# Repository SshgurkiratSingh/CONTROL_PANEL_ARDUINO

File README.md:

# Software-Defined Hardware Control Panel (SDH-CP)

An integrated, multi-interface hardware control platform that bridges physical inputs, microcontrollers, desktop GUIs, and web services. The project features an **Arduino-based firmware** with a rotary encoder and I2C OLED display, a **KiCad PCB design**, a **Python Tkinter Desktop GUI** featuring a background **Flask REST API**, and a **MATLAB dashboard**.

---

## Repository Structure

```directory
├── Software-Defined Hardware Control Panel/ # KiCad PCB & Schematic Design Files
│   ├── Software-Defined Hardware Control Panel.kicad_sch  # KiCad Schematic
│   ├── Software-Defined Hardware Control Panel.kicad_pcb  # KiCad PCB Layout
│   └── bom/
│       └── ibom.html                                       # Interactive Bill of Materials (iBOM)
├── src/                                     # Arduino C++ Firmware Source
│   ├── main.cpp                             # Main firmware loop and state machine
│   ├── helpers.cpp                          # RAM and hardware utility helpers
│   └── helpers.h                            # Circular Parameter Store class definitions
├── lib/                                     # Custom Hardware Libraries
│   └── ssd1306_128x64_i2c/                  # Optimized SSD1306 OLED display driver
├── include/                                 # PlatformIO headers directory
├── platformio.ini                           # PlatformIO Project Configuration
├── writeCommand.py                          # Python Tkinter GUI & Flask REST API Service
├── arduinoAMC.mlapp                         # MATLAB App Designer control panel/dashboard
├── package.json                             # Node.js dependencies (serialport tools)
└── README.md                                # Project Documentation (This file)
```

---

## Key Features

### Firmware (Arduino Uno + C++)
- **Dynamic Parameter Store**: Manages up to 5 runtime parameters (e.g., setpoints, configuration coefficients) with safety bounds (minimum and maximum).
- **Dual Display Modes**:
  - `MODE_FULL`: Shows the parameter name, current value, visual progress bar, and active connected software name.
  - `MODE_RAPID`: Switches to large-format value-only rendering during quick rotary encoder scrolls, reducing display redraw lag and maximizing responsiveness.
- **Hardware Integration**: Uses interrupt/tick-based rotary encoder tracking and switch inputs.
- **Real-Time Remote Control**: Provides a clean CSV-style serial communication protocol running at 9600 baud.

### Python GUI & REST API Daemon (writeCommand.py)
- **Desktop Console**: Multi-tab GUI for adding, reading, and updating parameters in real time. Contains a live serial traffic log and manual serial command terminal.
- **On-Demand Pin Reader**: Direct interface to read analog (A0-A5) and digital (D2-D13) pins on the fly.
- **REST API Backend**: Exposes a background Flask HTTP server on port `5000` to allow web apps or script automation to read and modify hardware states over simple network requests.

### Hardware Design (KiCad)
- Complete schematic and PCB design files for a dedicated control panel shield/device.
- **Interactive BOM (iBOM)** included (`ibom.html`) for easy assembly and soldering.

#### Hardware Gallery

| PCB 3D Render | PCB Routing |
| :---: | :---: |
|  |  |

| Schematic Diagram |
| :---: |
|  |

### MATLAB Integration (arduinoAMC.mlapp)
- Companion app for control, automation, and visualization of parameter values directly in MATLAB.

---

## Serial Communication Protocol

The Arduino firmware communicates with host computers via **9600 baud serial connection**. Messages use a command-response format:

### Host Commands (Commands sent to Arduino)

| Command Format | Description | Example |
| :--- | :--- | :--- |
| `add:param,<name>,<min>,<max>,<cur>` | Register/Overwrite a parameter in the store | `add:param,Gain,0,100,50` |
| `get:paramCurval,<name>` | Query the current value of a parameter | `get:paramCurval,Gain` |
| `update:paramsCurval,<name>,<val>` | Force-update a parameter value | `update:paramsCurval,Gain,65` |
| `get:AlladdedParams` | List all parameters in the store | `get:AlladdedParams` |
| `set:software,<name>` | Display active host software on the OLED | `set:software,MATLAB_App` |
| `read:digital,<pin>` | Set digital `<pin>` to input and read state | `read:digital,7` |
| `read:analog,<index>` | Read analog pin value (A0 + `<index>`) | `read:analog,0` |

### Arduino Responses & Broadcasts

| Response Prefix | Meaning | Format / Response Example |
| :--- | :--- | :--- |
| `A,<name>` | Parameter successfully added | `A,Gain` |
| `U,<name>,<val>` | Parameter updated (via encoder or serial command) | `U,Gain,65` |
| `S,<index>,<name>,<val>` | Active parameter selection cycled (via button press) | `S,0,Gain,65` |
| `G,<name>,<val>` | Parameter query result | `G,Gain,65` |
| `L,<idx>,<name>,<min>,<max>,<val>` | Parameter listing detail | `L,0,Gain,0,100,65` |
| `D,<pin>,<val>` | Digital pin read result | `D,7,1` |
| `A,<index>,<val>` | Analog pin read result | `A,0,512` |
| `ERR,<message>` | Command processing error | `ERR,Unknown command` |

---

## REST API Documentation

When running `writeCommand.py`, a Flask API server starts automatically at `http://localhost:5000`.

### Endpoints

#### 1. Get All Parameters
- **URL**: `/parameters`
- **Method**: `GET`
- **Response Example**:
  ```json
  {
    "Gain": {
      "index": "0",
      "min": "0",
      "max": "100",
      "current": 65
    }
  }
  ```

#### 2. Get Single Parameter
- **URL**: `/parameter/<name>`
- **Method**: `GET`
- **Response Example**:
  ```json
  {
    "Gain": {
      "index": "0",
      "min": "0",
      "max": "100",
      "current": 65
    }
  }
  ```

#### 3. Add Parameter
- **URL**: `/parameters`
- **Method**: `POST`
- **Headers**: `Content-Type: application/json`
- **Payload**:
  ```json
  {
    "name": "Frequency",
    "min": 10,
    "max": 1000,
    "current": 100
  }
  ```
- **Response**: `{"status": "Command sent", "command": "..."}`

#### 4. Update Parameter Value
- **URL**: `/parameter/<name>`
- **Method**: `PUT`
- **Headers**: `Content-Type: application/json`
- **Payload**:
  ```json
  {
    "new_value": 75
  }
  ```
- **Response**: `{"status": "Command sent", "command": "..."}`

#### 5. Send Raw Serial Command
- **URL**: `/command`
- **Method**: `POST`
- **Payload**: `{"command": "read:analog,0"}`
- **Response**: `{"status": "Command sent", "command": "..."}`

#### 6. Set Active Software Name
- **URL**: `/software`
- **Method**: `POST`
- **Payload**: `{"software_name": "API_Client"}`

#### 7. Retrieve Live GUI Console Log
- **URL**: `/log`
- **Method**: `GET`
- **Response**: `{"log": "..."}`

---

## Setup and Installation

### 1. Hardware Assembly
- Open the KiCad project files inside `Software-Defined Hardware Control Panel/` in KiCad.
- Reference the interactive BOM under `bom/ibom.html` for component lists and layout locations.
- Connect an I2C SSD1306 OLED screen to pins `SDA` (A4) and `SCL` (A5) of your Arduino.
- Connect a Rotary Encoder:
  - CLK to Pin 3 (Interrupt enabled)
  - DT to Pin 4
  - Push Button to Pin 2 (Interrupt/cycle pin)

### 2. Firmware Installation (VS Code + PlatformIO)
1. Open the project folder in VS Code with the **PlatformIO IDE** extension installed.
2. PlatformIO will fetch dependencies (`mathertel/RotaryEncoder`, `bblanchon/ArduinoJson`) automatically.
3. Build and upload:
   ```bash
   pio run --target upload
   ```

### 3. Desktop GUI & REST API Setup
Install python dependencies:
```bash
pip install pyserial flask
```
Identify your Arduino serial port (e.g. `/dev/ttyUSB0` on Linux or `COM3` on Windows). Update the default port at the bottom of `writeCommand.py` or launch the script:
```bash
python writeCommand.py
```

### 4. MATLAB Integration
- Launch MATLAB.
- Double-click and open `arduinoAMC.mlapp` in the App Designer to run the companion dashboard.

---

> [!NOTE]
> Ensure that no other program (such as VS Code Serial Monitor or MATLAB) is occupying the serial port when executing `writeCommand.py`, as only one application can hold the serial connection handle at a time.

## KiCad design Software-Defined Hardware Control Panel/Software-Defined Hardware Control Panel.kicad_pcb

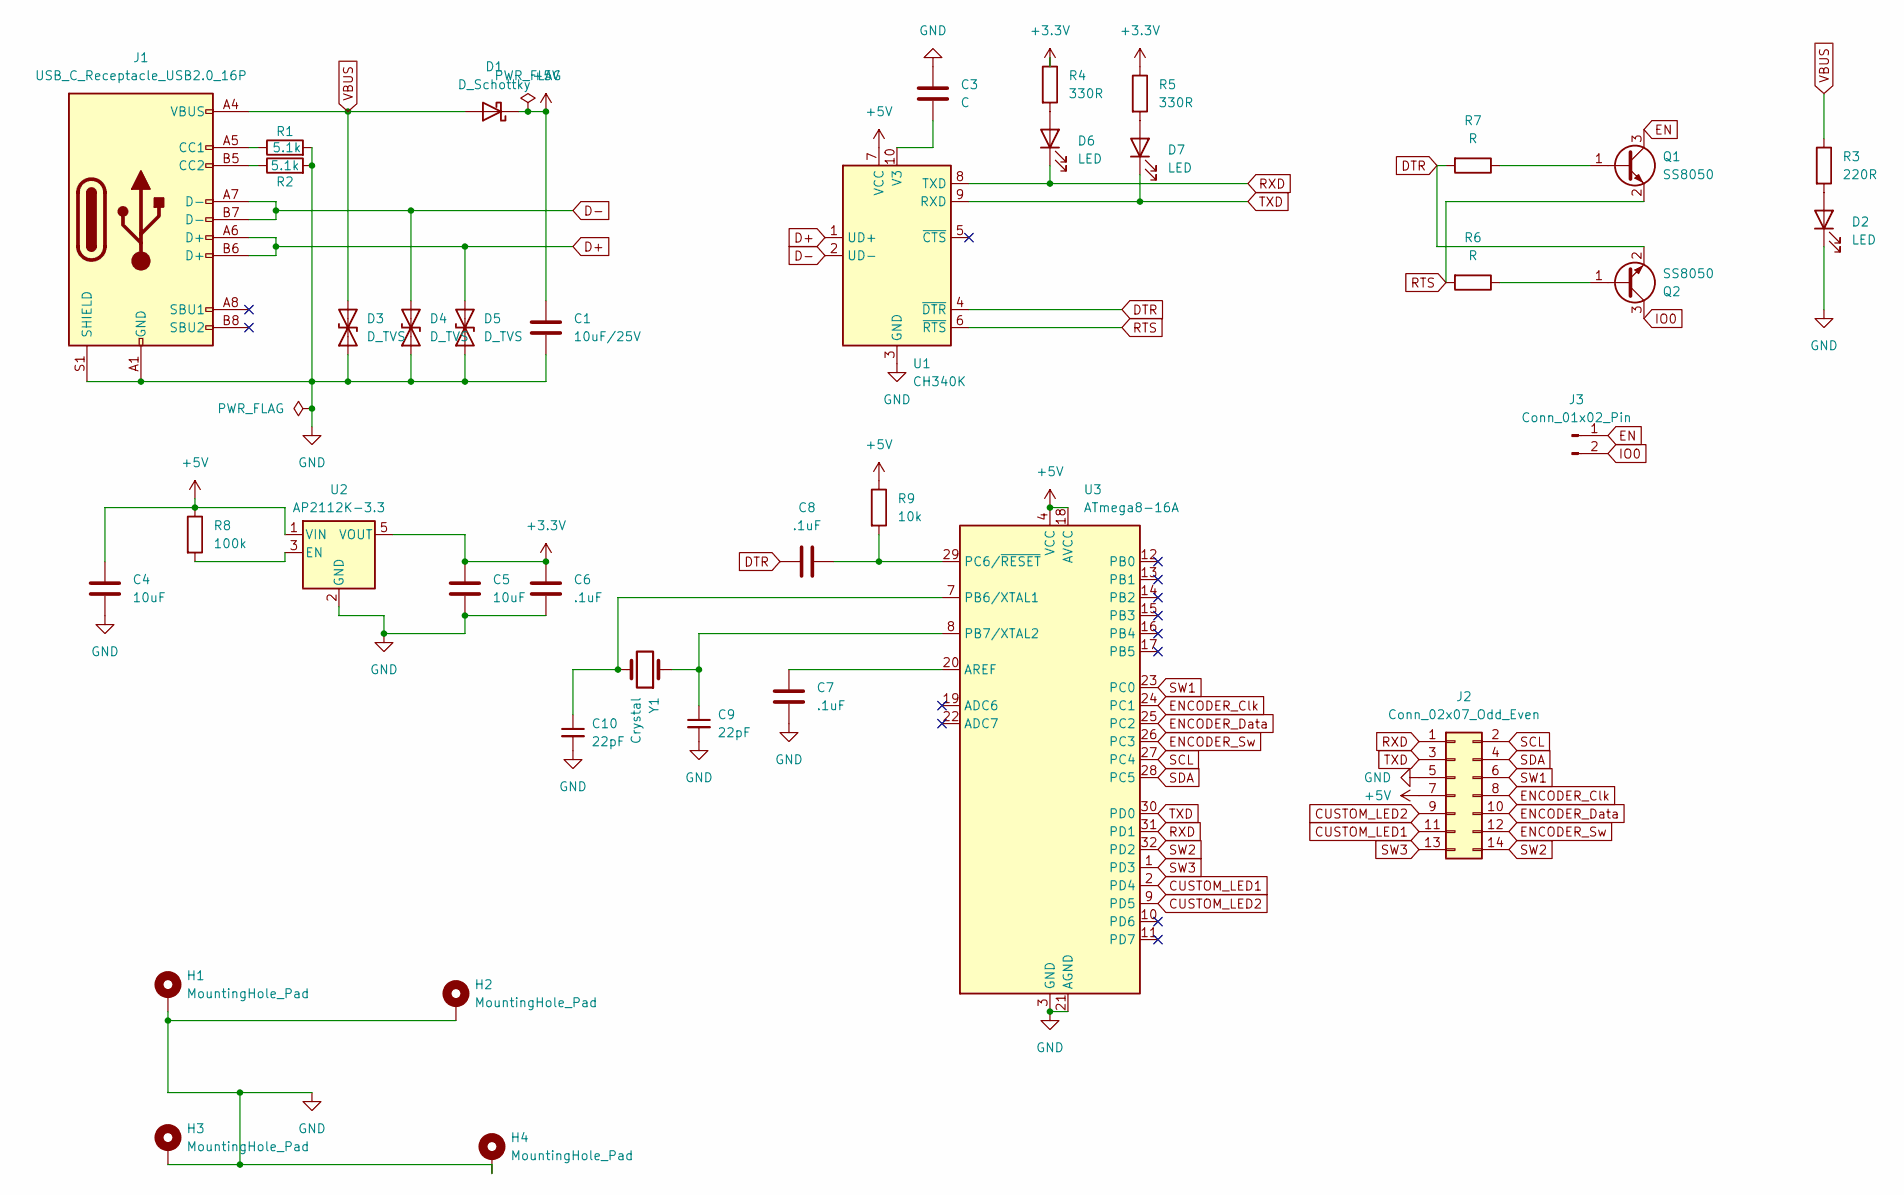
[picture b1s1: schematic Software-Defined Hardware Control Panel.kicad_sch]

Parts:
C1: 10uF/25V; C_0805_2012Metric
C3: C; C_0805_2012Metric
C4, C5: 10uF; C_0805_2012Metric
C6, C7, C8: .1uF; C_0805_2012Metric
C9, C10: 22pF; C_0805_2012Metric
D1: D_Schottky; D_SOD-123
D2, D6, D7: LED; LED_0805_2012Metric_Pad1.15x1.40mm_HandSolder
D3, D4, D5: D_TVS; D_SOD-523
H1, H2, H3, H4: MountingHole_Pad; MountingHole_3.2mm_M3_Pad
J1: USB_C_Receptacle_USB2.0_16P; USB_C_Receptacle_XKB_U262-16XN-4BVC11
J2: Conn_02x07_Odd_Even; JST_GH_BM14B-GHS-TBT_1x14-1MP_P1.25mm_Vertical
J3: Conn_01x02_Pin; JST_EH_B2B-EH-A_1x02_P2.50mm_Vertical
Q1, Q2: SS8050; SOT-23
R1, R2: 5.1k; R_0805_2012Metric
R3: 220R; R_0805_2012Metric
R4, R5: 330R; R_0805_2012Metric
R6, R7: R; R_0805_2012Metric
R8: 100k; R_0805_2012Metric
R9: 10k; R_0805_2012Metric
U1: CH340K; SSOP-10-1EP_3.9x4.9mm_P1mm_EP2.1x3.3mm
U2: AP2112K-3.3; SOT-23-5
U3: ATmega8-16A; TQFP-32_7x7mm_P0.8mm
Y1: Crystal; Crystal_SMD_HC49-SD

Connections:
+3.3V: C5.1, C6.1, R4.1, R5.1, U2.5 (VOUT)
+5V: C1.1, C4.1, D1.1 (K), J2.7, R8.1, R9.1, U1.7 (VCC), U2.1 (VIN), U3.4 (VCC), U3.6 (VCC), U3.18 (AVCC)
CUSTOM_LED1: J2.11, U3.2 (PD4)
CUSTOM_LED2: J2.9, U3.9 (PD5)
D+: D5.2 (A2), J1.A6 (D+), J1.B6 (D+), U1.1 (UD+)
D-: D4.2 (A2), J1.A7 (D-), J1.B7 (D-), U1.2 (UD-)
DTR: C8.2, Q2.2 (E), R7.2, U1.4 (~DTR)
EN: J3.1, Q1.3 (C)
ENCODER_Clk: J2.8, U3.24 (PC1)
ENCODER_Data: J2.10, U3.25 (PC2)
ENCODER_Sw: J2.12, U3.26 (PC3)
GND: C1.2, C3.1, C4.2, C5.2, C6.2, C7.2, C9.2, C10.2, D2.1 (K), D3.1 (A1), D4.1 (A1), D5.1 (A1), H1.1, H2.1, H3.1, H4.1, J1.A1 (GND), J1.A12 (GND), J1.B1 (GND), J1.B12 (GND), J1.S1 (SHIELD), J2.5, R1.2, R2.2, U1.3 (GND), U1.11 (GND), U2.2 (GND), U3.3 (GND), U3.5 (GND), U3.21 (AGND)
IO0: J3.2, Q2.3 (C)
unnamed: D2.2 (A), R3.2
unnamed: D6.2 (A), R4.2
unnamed: D7.2 (A), R5.2
unnamed: J1.A5 (CC1), R1.1
unnamed: J1.B5 (CC2), R2.1
unnamed: Q1.1 (B), R7.1
unnamed: Q2.1 (B), R6.1
unnamed: C3.2, U1.10 (V3)
unnamed: R8.2, U2.3 (EN)
unnamed: C7.1, U3.20 (AREF)
unnamed: C10.1, U3.7 (PB6/XTAL1), Y1.2
unnamed: C9.1, U3.8 (PB7/XTAL2), Y1.1
unnamed: C8.1, R9.2, U3.29 (PC6/~RESET)
RTS: Q1.2 (E), R6.2, U1.6 (~RTS)
RXD: D6.1 (K), J2.1, U1.8 (TXD), U3.31 (PD1)
SCL: J2.2, U3.27 (PC4)
SDA: J2.4, U3.28 (PC5)
SW1: J2.6, U3.23 (PC0)
SW2: J2.14, U3.32 (PD2)
SW3: J2.13, U3.1 (PD3)
TXD: D7.1 (K), J2.3, U1.9 (RXD), U3.30 (PD0)
VBUS: D1.2 (A), D3.2 (A2), J1.A4 (VBUS), J1.A9 (VBUS), J1.B4 (VBUS), J1.B9 (VBUS), R3.1

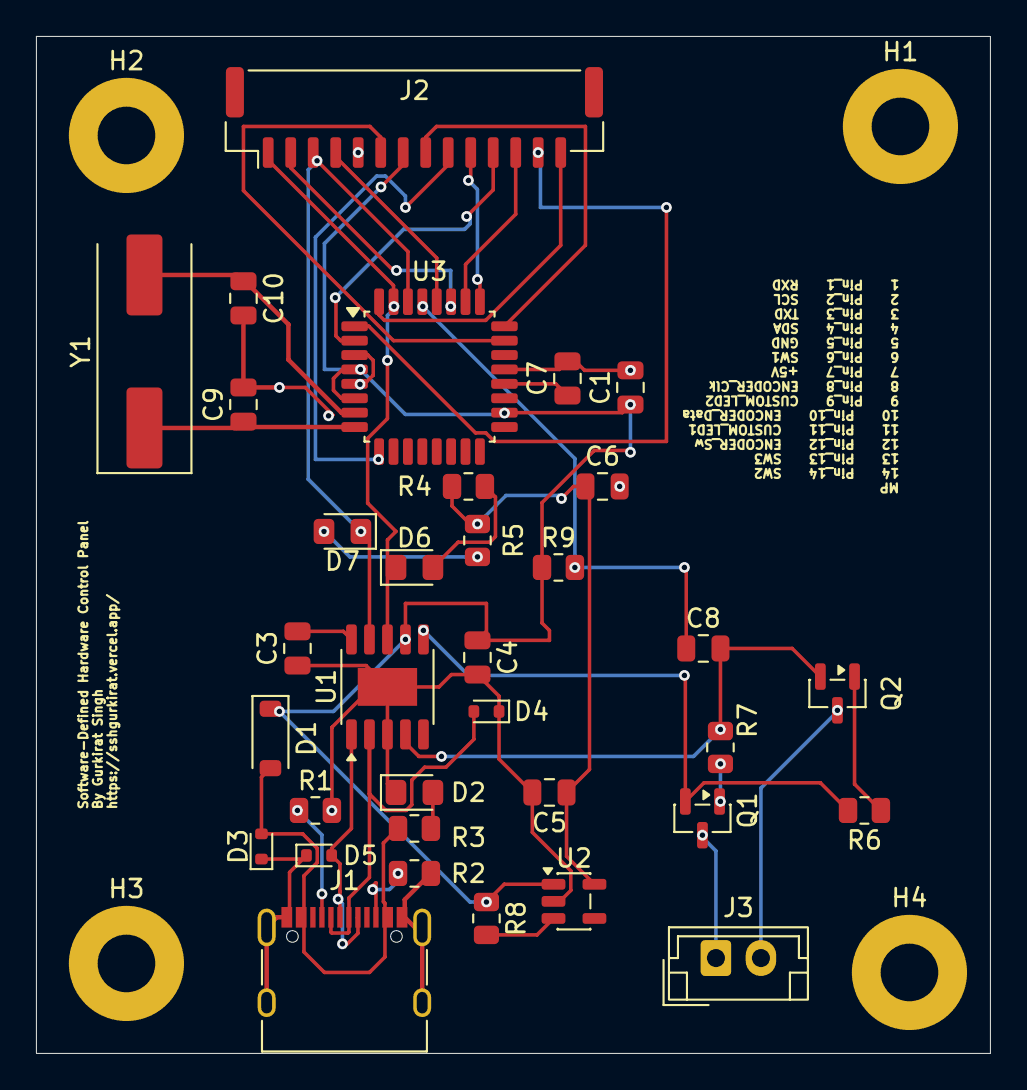
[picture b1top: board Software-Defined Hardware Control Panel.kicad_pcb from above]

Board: 2 copper layers, 53.0 x 56.5 mm, 38 parts (0 on the bottom side), 35 nets.

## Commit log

2025-03-15 init
2025-03-15 init2
2026-06-19 readme
